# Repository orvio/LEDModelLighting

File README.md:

# LEDModelLighting
A small library to control LEDs lighting effects in building models on model railroads an similar purposes.

## Installation
Simply copy all the .cpp and .h files into a subdirectory of your Arduino library folder.
On windows that folder is usually located under Documents/Arduino/libraries.

After copying the files into your library folder you need to restart the Arduino IDE.

## Usage
The full API documention is at: https://orvio.github.io/LEDModelLighting/

After installing the library files simply put
```#include <LEDLightingCycle.h>```
at the start of you sketch to be able to use the library functions.

The easiest way to get started is to create a new sketch and replace the entire content of the sketch with this code:
```
#include <LEDLightingCycle.h>

//define number of LEDs
#define LED_COUNT 1

//LED setup
LEDStaticLighting * ledSetups[LED_COUNT];

void setup() {
  ledSetups[0] = new LEDRandomLightingCycle(LED_BUILTIN, 255, 500, 1000, 1000, 2000, new LEDCyclicEffect(), new FluorescentStartEffect(100, 500), new FadeEffect(100, FADE_OUT));
}

void loop() {
  // put your main code here, to run repeatedly:
  for (unsigned char ledIndex = 0; ledIndex < LED_COUNT; ledIndex++) {
    ledSetups[ledIndex]->execute();
  }
}
```

This will control the on board LED of your Arduino, so you don't need any additional hardware. This code will cycle between on and off with a random duration for the on and off state.
The LED will turn on for a time between 500ms ad 1000ms and turn off for a time between 1000 ad 2000 ms.
When the light is activated a fluorescent startup flicker simulation executes for a time between 100 and 500ms.
Then the light is deactivated it will fade from bright to dark within 100ms.

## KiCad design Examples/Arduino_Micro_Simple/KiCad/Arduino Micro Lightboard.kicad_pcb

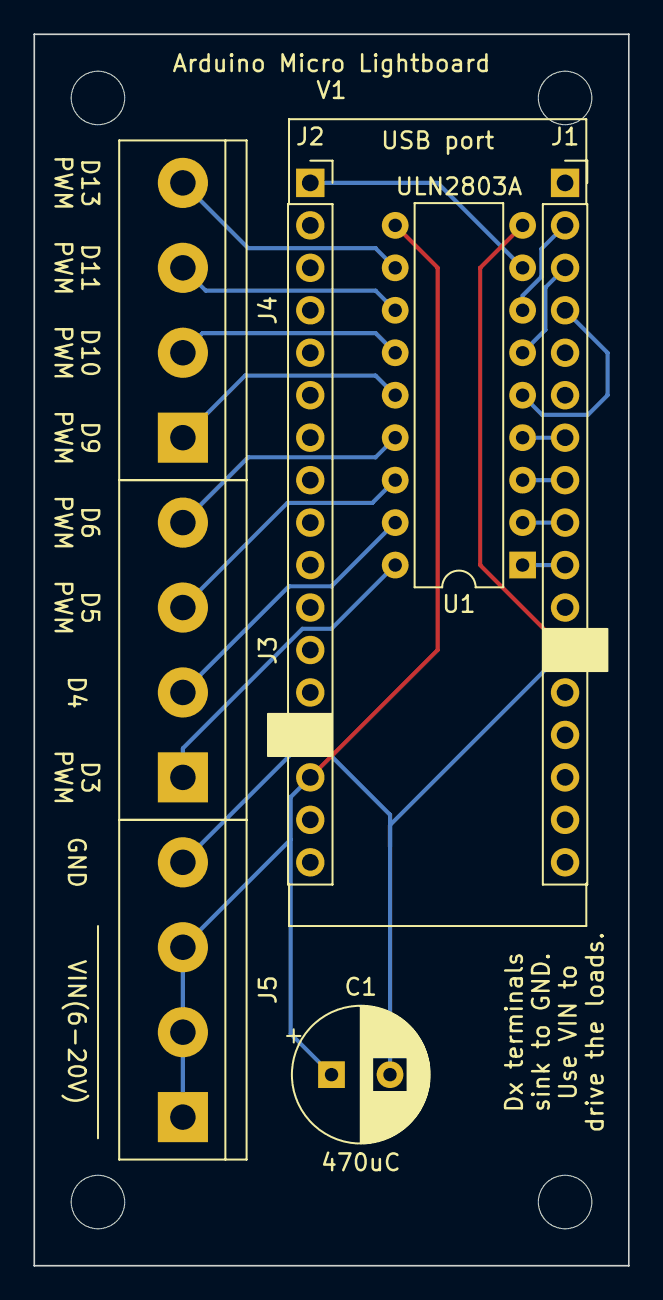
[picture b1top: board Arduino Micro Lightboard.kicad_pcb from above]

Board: 2 copper layers, 35.6 x 73.7 mm, 7 parts (0 on the bottom side), 18 nets.

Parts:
C1: 470uC; CP_Radial_D8.0mm_P3.50mm
J1, J2: Conn_01x17_Female; PinSocket_1x17_P2.54mm_Vertical
J3, J4, J5: Screw_Terminal_01x04; TerminalBlock_bornier-4_P5.08mm
U1: ULN2803A; DIP-18_W7.62mm

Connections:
+7.5V: C1.1, J2.15, J5.1, J5.2, J5.3, U1.10
/D3(PWM): J1.10, U1.1
/D3_OUT: J3.1, U1.18
/D4: J1.9, U1.2
/D4_OUT: J3.2, U1.17
/D5(PWM): J1.8, U1.3
/D5_OUT: J3.3, U1.16
/D6(PWM): J1.7, U1.4
/D6_OUT: J3.4, U1.15
/D9(PWM): J1.4, U1.5
/D9_OUT: J4.1, U1.14
/D10(PWM): J1.3, U1.6
/D10_OUT: J4.2, U1.13
/D11(PWM): J1.2, U1.7
/D11_OUT: J4.3, U1.12
/D13(PWM): J2.1, U1.8
/D13_OUT: J4.4, U1.11
GND: C1.2, J1.12, J2.14, J5.4, U1.9

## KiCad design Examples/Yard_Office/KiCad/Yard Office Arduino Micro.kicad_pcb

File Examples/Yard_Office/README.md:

The circuit schematic for this example has been built on a prototype PCB with wires instead of a manufactured PCB (see images).

This means that the PCB layout in the KiCad folder should not be sent directly to a PCB manufacturing service.

This example sketch monitors the 5V and 7.5V VIN values and indicates the measured range with LEDs on the board in addition to the light control functions.
The yard office has three outside lights that are active permanently. The three illuminated rooms are on random cycles where the light is on for 5 to 15
minutes and then off for 5 to 15 minutes. One of the rooms monitors the status of another room and is only illuminated when the light of the monitored room is on.

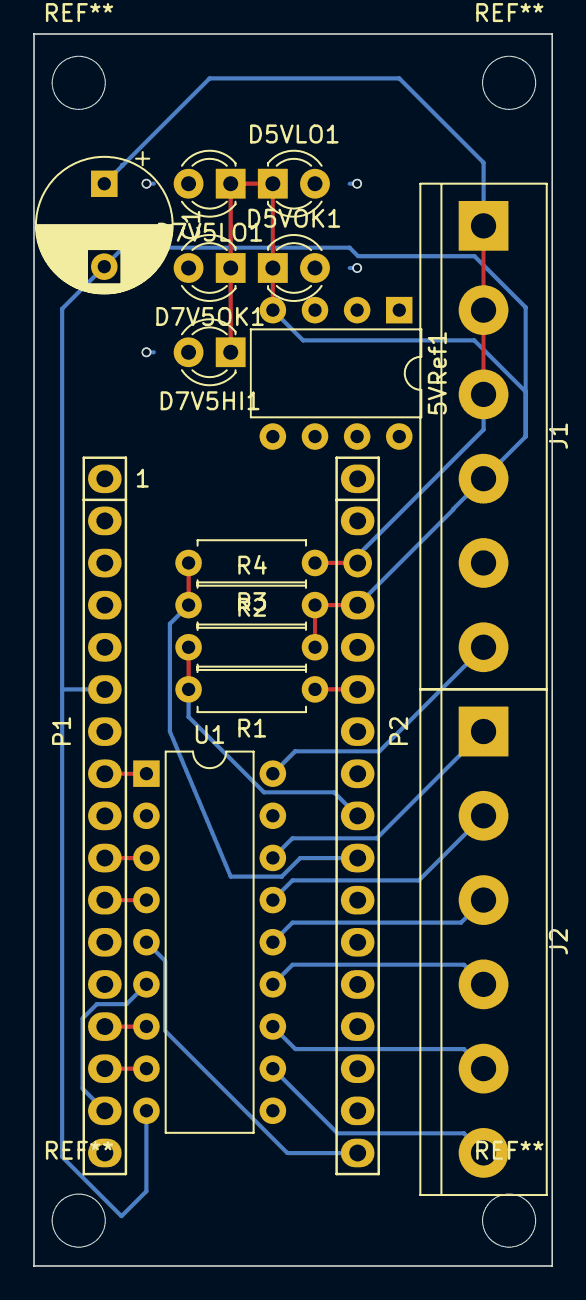
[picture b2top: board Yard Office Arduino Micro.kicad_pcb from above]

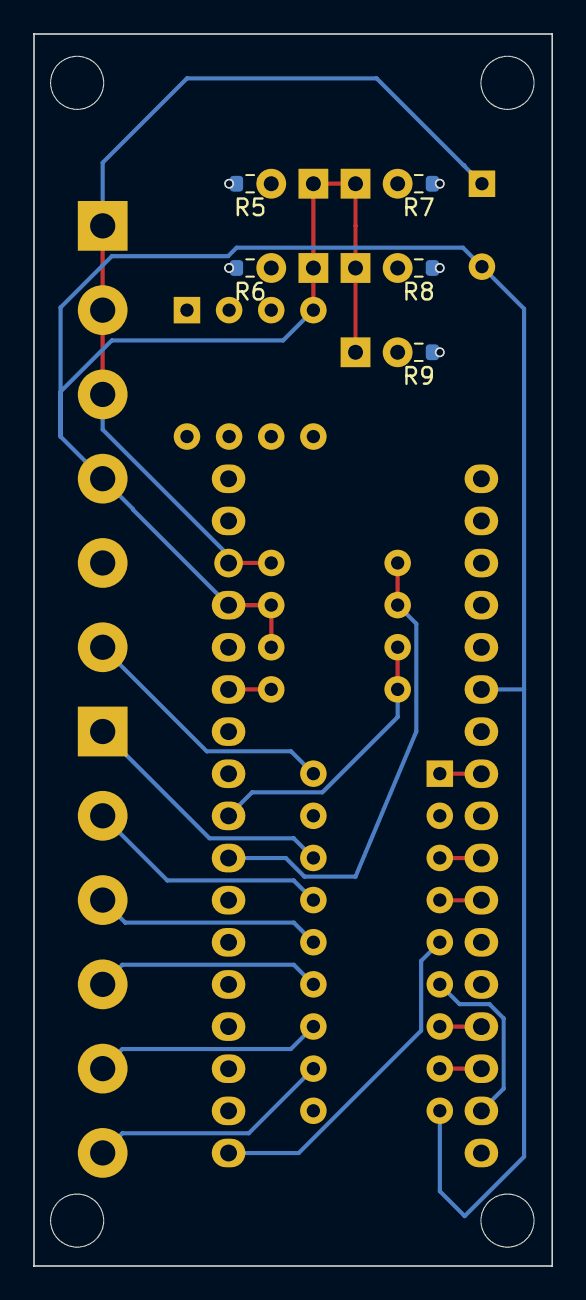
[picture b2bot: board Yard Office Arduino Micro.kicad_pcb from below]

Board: 4 copper layers, 31.2 x 74.3 mm, 21 parts (5 on the bottom side), 31 nets.

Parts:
5VRef1: LT1021-5; DIP-8_W7.62mm
C1: 470uF; CP_Radial_D8.0mm_P5.00mm
D5VLO1, D5VOK1, D7V5HI1, D7V5LO1, D7V5OK1: LED; LED_D3.0mm
J1, J2: TerminalBlock_bornier-6_P5.08mm
P1: Digital; Socket_Strip_Arduino_1x17
P2: Analog; Socket_Strip_Arduino_1x17
R1, R2, R4: 10kR; R_Axial_DIN0207_L6.3mm_D2.5mm_P7.62mm_Horizontal
R3: 22kR; R_Axial_DIN0207_L6.3mm_D2.5mm_P7.62mm_Horizontal
R5, R6, R7, R8, R9: 1kR; R_0603_1608Metric
U1: ULN2803A; DIP-18_W7.62mm

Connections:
+5V: P2.6, R1.1
+7.5V: 5VRef1.2, C1.1, J1.1, J1.2, J1.3, P2.3, R3.1
/5(**): P1.10, U1.3
/6(**/A7): P1.11, U1.4
/7(7V5LOIO): P1.12, R7.1
/8(7V5OKIO): P1.13, R8.1
/9(**/A9): P1.14, U1.7
/10(**\A10): P1.15, U1.8
/11(**): P1.16, U1.6
/12(7V5HIIO): P1.17, R9.1
/13(**): P2.17, U1.5
/A2(D5VLOIO): P2.12, R5.2
/A3(D5VOKIO): P2.11, R6.2
/A4(7V5MEAS): P2.10, R3.2, R4.1
/A5(5VMEAS): P2.9, R1.2, R2.1
/AREF: 5VRef1.6, P2.15
/DO3(PWM): P1.8, U1.1
/EffectLED1: J2.6, U1.11
/EffectLED2: J2.5, U1.12
/EffectLED3: J2.4, U1.13
/EffectLED4: J2.3, U1.14
/EffectLED5: J2.2, U1.15
/EffectLED6: J2.1, U1.16
/EffectLED7: J1.6, U1.18
/Reset: P1.5, P2.5
GND: 5VRef1.4, C1.2, D5VLO1.1, D5VOK1.1, D7V5HI1.1, D7V5LO1.1, D7V5OK1.1, J1.4, P1.6, P2.4, R2.2, R4.2, U1.9
unnamed: D5VLO1.2, R5.1
unnamed: D5VOK1.2, R6.1
unnamed: D7V5HI1.2, R9.2
unnamed: D7V5LO1.2, R7.2
unnamed: D7V5OK1.2, R8.2

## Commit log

2021-09-18 Initial files
2021-09-18 Added license notice
2021-09-18 Removed redudant implementation in LEDLightingCycle
2021-09-18 Changed default state to OFF to avoid flash on start
2021-09-18 Added optional delay for transition effects
2021-09-19 added pinMode() call to LEDStaticLighting contructor
2021-09-19 Added basic installtion and usage instructions
2021-09-19 Corrected example code
2021-09-23 Create Doxyfile
2021-09-23 changed branch to main
2021-09-23 Update Doxyfile
2021-09-23 added link to doxygen documentation
2021-09-26 Updated LEDLightingCycle documentation
2021-09-26 Updated documentation
2021-10-03 fixed typo in documentation
2021-10-03 Added LEDTriggeredCycle
2021-10-04 Replaced defines with enums
2021-10-04 Deploy orvio/LEDModelLighting to github.com/orvio/LEDModelLighting.git:gh-pages
2021-10-05 Fixed typo
2021-10-05 Fixed documentation
2021-10-05 deploy: f7507e9aa1f6800a3952bac240cdd0f1fbc517a9
2021-10-05 deploy: ef62316331f52e2611fe529e871008373ade7647
2021-10-05 Removed travis ci integration
2021-10-10 implemented LEDChainedCycle
2021-10-10 deploy: 6c9a54055581a7b8dc1f6257b953daa9f01bdc91
2021-10-10 now using bool instead of char for return value
2021-10-10 removed test workflow
2021-10-10 deploy: ba1cc1974fdc8e525047ffcd69c40b062257a4c9
2021-10-12 Added wiring documentation
    Added KiCad wiring documentation for yard office arduino
2021-10-12 Moved KiCad files into the example folder
2021-11-04 Fixed pin assignments
2021-11-04 Fixed #include for arduino.h on Linux
    now using Arduino.h instead of arduino.h
2022-01-04 Added Arduino Nano V2 Lightboard files
2022-01-06 Added readme
2022-01-06 Added Arduino Micro lightboard files
2022-01-06 Added Arduino Nano example sketch
